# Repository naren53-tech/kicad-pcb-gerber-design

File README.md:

# kicad-pcb-gerber-design
Designed a PCB and generated Gerber files for manufacturing using KiCad
# 🛠️ PCB Design & Gerber Generation using KiCad

## 📌 Project Overview

This project demonstrates the design of a printed circuit board (PCB) using KiCad and the generation of Gerber files required for manufacturing.

---

## 🧰 Tools Used

* KiCad (Schematic & PCB Design)

---

## 🔄 Workflow

1. Created schematic in KiCad
2. Converted schematic to PCB layout
3. Routed tracks and finalized board design
4. Defined board outline using Edge.Cuts layer
5. Generated Gerber files for fabrication
6. Exported drill files (PTH & NPTH)

---

## 📁 Generated Files

* Top Copper (F.Cu.gbr)
* Bottom Copper (B.Cu.gbr)
* Board Outline (Edge_Cuts.gbr)
* Drill Files (.drl, PTH, NPTH)

---

## 📸 PCB Design Preview

(Add your PCB layout screenshots here)

---

## 🎯 Key Learning Outcomes

* PCB layout design using KiCad
* Understanding Gerber file structure
* Preparing files for PCB manufacturing
* Layer management and drill configuration

---

## 🚀 Future Scope

* CNC PCB fabrication using CopperCAM & Mach3
* Multi-layer PCB design
* Surface mount component integration

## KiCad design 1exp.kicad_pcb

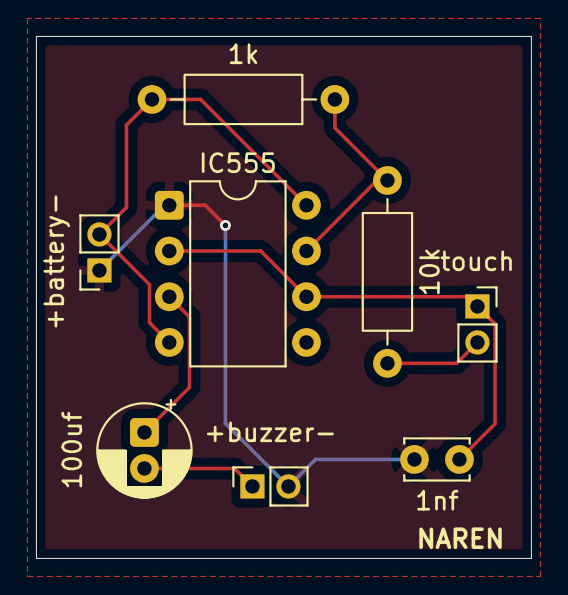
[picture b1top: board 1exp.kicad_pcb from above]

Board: 2 copper layers, 27.5 x 29.0 mm, 8 parts (0 on the bottom side), 7 nets.

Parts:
1k: R; R_Axial_DIN0207_L6.3mm_D2.5mm_P10.16mm_Horizontal
1nf: C; C_Disc_D3.4mm_W2.1mm_P2.50mm
10k: 1k; R_Axial_DIN0207_L6.3mm_D2.5mm_P10.16mm_Horizontal
100uf: C_Polarized_Small; CP_Radial_D5.0mm_P2.00mm
+battery-: battery; PinSocket_1x02_P2.00mm_Vertical
+buzzer-: buzzer; PinSocket_1x02_P2.00mm_Vertical
IC555: NE555P; DIP-8_W7.62mm
touch: touch; PinSocket_1x02_P2.00mm_Vertical

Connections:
GND: 1nf.2, +battery-.1, +buzzer-.2, IC555.1 (GND)
unnamed: 100uf.2, +buzzer-.1
unnamed: 10k.2, touch.2
unnamed: 1k.1, 10k.1, IC555.7 (DISCH)
unnamed: 100uf.1, IC555.3 (OUT)
unnamed: 1nf.1, IC555.2 (TRIG), IC555.6 (THRES), touch.1
VCC: 1k.2, +battery-.2, IC555.4 (~RST), IC555.8 (VCC)

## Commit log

2026-05-02 Enhance README with detailed project information
    Expanded README to include project overview, tools used, workflow, generated files, key learning outcomes, and future scope.
2026-05-02 Add files via upload
    Added PCB design and Gerber files
